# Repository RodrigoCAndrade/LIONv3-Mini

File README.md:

<div align="center">
  
</div>

<h1 align="center">LIONv3-Mini Module</h1>

<p align="center">

</p>

<br>

## Overview

The LIONv3-Mini is a miniaturized version of the [LIONv3-R](https://github.com/RodrigoCAndrade/LIONv3-Mini), without an onboard LoRa PCB antenna. Built around the ESP32-C6 with 16 MB of external flash, it offers local connectivity over Wi-Fi, Zigbee and Thread, plus LoRa and LR-FHSS for reliable Direct-to-Satellite (DtS) or terrestrial uplinks from remote sites at higher device densities than conventional LoRa. It is a scalable platform for telemetry, global asset tracking and remote sensing.

## Repository Organization

* `docs`: Systems engineering documentation, including schematics, datasheets, requirements (SRD), interface control (ICD) and diagrams.
* `hardware`: Native KiCad project and manufacturing files.
* `mechanics`: 3D models, technical drawings, and physical integration constraints.
* `software`: Embedded firmware and support testing scripts.

## Releases

<table>
  <thead>
    <tr>
      <th>Render</th>
      <th>Hardware Revision</th>
      <th>Status</th>
      <th>Latest Release</th>
      <th>Date</th>
      <th>Datasheet</th>
      <th>BOM</th>
      <th>Manufacturing Info</th>
    </tr>
  </thead>
  <tbody>
    <tr>
      <td></td>
      <td>LIONv3-Mini</td>
      <td>🚧 Development</td>
      <td><a href="#">-</a></td>
      <td>05-10-2026</td>
      <td><a href="#">PDF</a></td>
      <td><a href="hardware/Fabrication/BOM-LIONv3.csv">Available</a></td>
      <td><a href="hardware/Fabrication/GERBER-LIONv3.zip">Gerber</a></td>
    </tr>
  </tbody>
</table>

## Fabrication

This board is intended to be fabricated at [JLCPCB](https://jlcpcb.com/). The Gerber files, position files and BOM are available. For complete instructions, see the [Fabrication Guide](hardware/Fabrication/LIONv3-Mini%20Fabrication%20Guide.pdf). Please note that we do not guarantee the board will work, and any manufacturing issues are the user's responsibility. If you find an error or have suggestions for improvement, please do not hesitate to contribute.

## Contributing

We welcome contributions to this project! To ensure a smooth collaboration and maintain our engineering standards, please review our [Contribution Guidelines](CONTRIBUTING.md) before opening any issues, modifying the hardware design, or submitting pull requests.

## References

This board was developed from scratch, but draws on the earlier LIONv1 and LIONv2 designed by [Diego Anestor Coutinho](https://github.com/DIEGOVZK) and [Arielli Ajudarte](https://github.com/ari-aju). The v3 introduces several improvements:

- Dedicated low-power MCU on board
- LR-FHSS support and a more capable LoRa transceiver, covering both sub-GHz and S-band
- External flash for store-and-forward applications
- More compact form factor

## License

This project utilizes a dual-licensing approach to maximize flexibility and adoption:

* **Hardware:** The hardware designs and schematics are licensed under the permissive **[CERN-OHL-P-2.0](hardware/LICENSE)** open-hardware license. You are entirely free to use, modify, distribute, and commercialize the design without any copyleft obligations to share your derived works under the same terms.
* **Software:** All embedded firmware and utility scripts are licensed under the **[MIT License](software/LICENSE)**. You are free to use, modify, and distribute the code without restriction, provided the original copyright notice and permission notice are included.

## Acknowledgments

This work was carried out at the National Institute of Telecommunications (Inatel) with the support of three research laboratories. The EMBRAPII Inatel Competence Center for 5G and 6G Networks [(xGMobile)](https://inatel.br/xgmobile/) supported this project through its Talent Development Program (PFT xGMobile), alongside the Radio & Communication Laboratory [(RadioCom Lab)](https://inatel.br/radiocomlab/) and the Wireless and Artificial Intelligence Laboratory [(WAI Lab)](https://inatel.br/wailab/). Many thanks to the researchers and staff of all three laboratories for their help and for the infrastructure that made the LIONv3-Mini possible.

<p align="center">
  <sub>Built with ❤️ by <a href="https://rodrigoandrade.com">Rodrigo de Carvalho Andrade</a></sub>
</p>

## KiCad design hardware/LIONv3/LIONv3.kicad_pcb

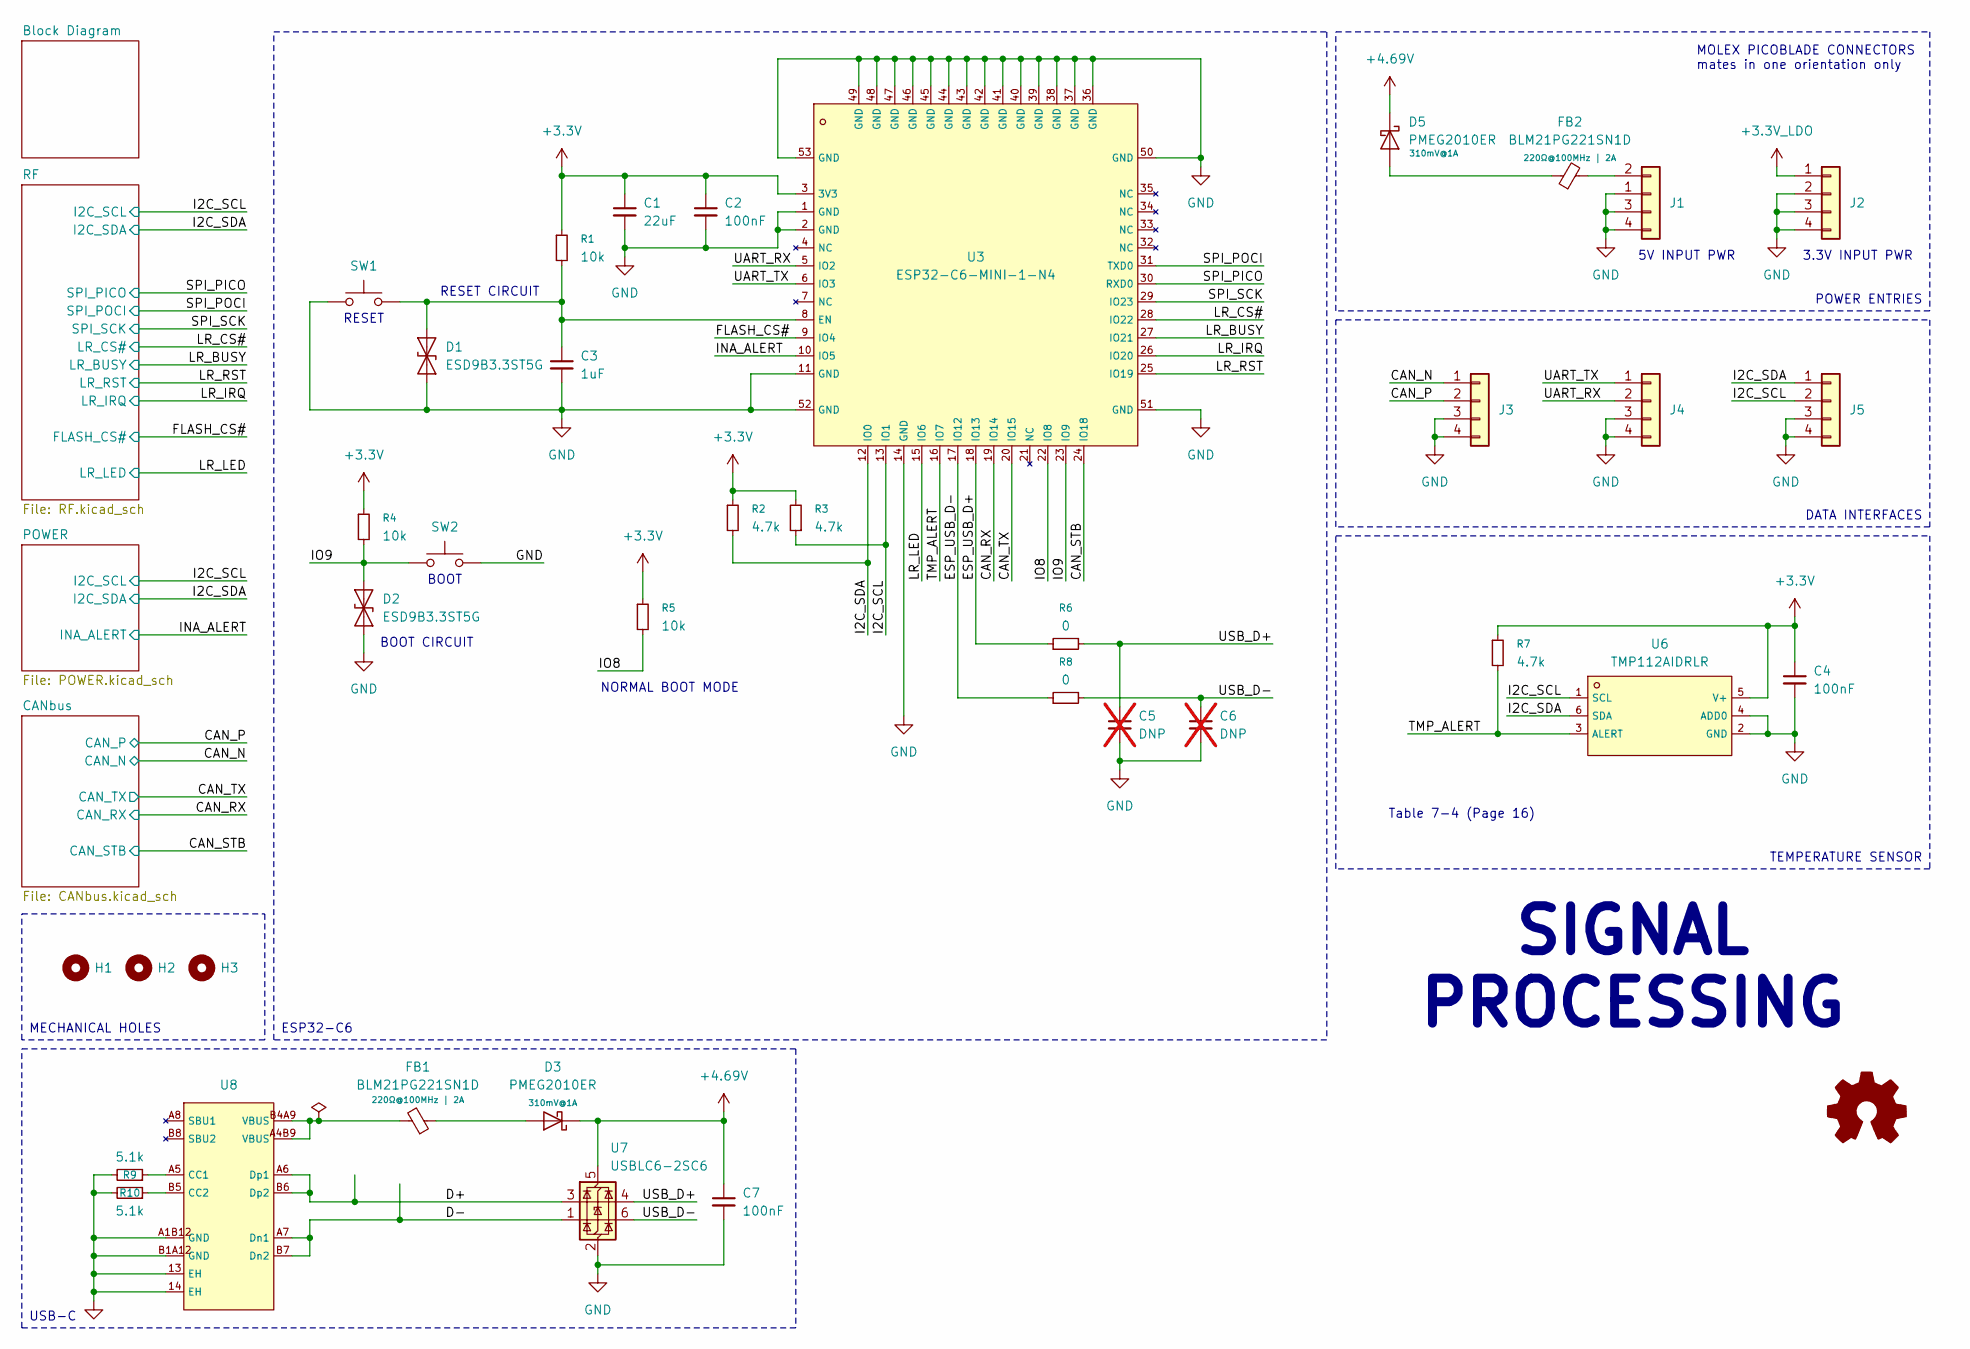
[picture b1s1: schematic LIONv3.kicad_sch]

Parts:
C1: 22uF; C_0805_2012Metric; LCSC C45783
C2, C4, C7: 100nF; C_0402_1005Metric; LCSC C307331
C3: 1uF; C_0603_1608Metric; LCSC C15849
C5, C6: DNP; C_0402_1005Metric; not fitted
D1, D2: ESD9B3.3ST5G; D_SOD-923; LCSC C96512
D3, D5: PMEG2010ER; Nexperia_CFP3_SOD-123W; Rating 310mV@1A; LCSC C82288
FB1, FB2: BLM21PG221SN1D; L_0805_2012Metric; Rating 220Ω@100MHz | 2A; LCSC C85840
H1, H2, H3: MountingHole_Pad; MountingHole_2.5mm
J1, J2, J3, J4, J5: 532610271; Molex_PicoBlade_53261-0271_1x02-1MP_P1.25mm_Horizontal; LCSC C177225
R1, R4, R5: 10k; R_0402_1005Metric; LCSC C25744
R2, R3, R7: 4.7k; R_0402_1005Metric; LCSC C25900
R6, R8: 0; R_0402_1005Metric; LCSC C17168
R9, R10: 5.1k; R_0402_1005Metric; LCSC C25905
S1: Logo_Open_Hardware_Small; OSHW-Logo2_14.6x12mm_SilkScreen
SW1, SW2: KEY-SMD_L3.9-W3.0-LS5.0; LCSC C5373431
U3: ESP32-C6-MINI-1-N4; ESP32-C6-MINI-1; LCSC C5736265
U6: TMP112AIDRLR; SOT-563_L1.6-W1.2-P0.50-LS1.6-BR; LCSC C28927
U7: USBLC6-2SC6; SOT-23-6; LCSC C7519
U8: TYPE-C_16PIN_2MD(073); USB-C-SMD_TYPE-C-16PIN-2MD-073; LCSC C2765186

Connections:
+3.3V: C1.1, C2.1, C4.1, R1.1, R2.1, R3.2, R4.1, R5.1, R7.1, U3.3 (3V3), U6.5 (V+); also elsewhere on the board
+3.3V_LDO: J2.1; also elsewhere on the board
+4.69V: C7.1, D3.1 (K), D5.1 (K), U7.5 (VBUS); also elsewhere on the board
/CAN_N: J3.1; also elsewhere on the board
/CAN_P: J3.2; also elsewhere on the board
/CAN_RX: U3.19 (IO14); also elsewhere on the board
/CAN_STB: U3.24 (IO18); also elsewhere on the board
/CAN_TX: U3.20 (IO15); also elsewhere on the board
/D+: U7.3 (I/O2), U8.A6 (Dp1), U8.B6 (Dp2)
/D-: U7.1 (I/O1), U8.A7 (Dn1), U8.B7 (Dn2)
/ESP_USB_D+: R6.1, U3.18 (IO13)
/ESP_USB_D-: R8.1, U3.17 (IO12)
/FLASH_CS#: U3.9 (IO4); also elsewhere on the board
/I2C_SCL: J5.2, R3.1, U3.13 (IO1), U6.1 (SCL); also elsewhere on the board
/I2C_SDA: J5.1, R2.2, U3.12 (IO0), U6.6 (SDA); also elsewhere on the board
/INA_ALERT: U3.10 (IO5); also elsewhere on the board
/IO8: R5.2, U3.22 (IO8)
/IO9: D2.2 (A2), R4.2, SW2.1, U3.23 (IO9)
/LR_BUSY: U3.27 (IO21); also elsewhere on the board
/LR_CS#: U3.28 (IO22); also elsewhere on the board
/LR_IRQ: U3.26 (IO20); also elsewhere on the board
/LR_LED: U3.15 (IO6); also elsewhere on the board
/LR_RST: U3.25 (IO19); also elsewhere on the board
/SPI_PICO: U3.30 (RXD0); also elsewhere on the board
/SPI_POCI: U3.31 (TXD0); also elsewhere on the board
/SPI_SCK: U3.29 (IO23); also elsewhere on the board
/TMP_ALERT: R7.2, U3.16 (IO7), U6.3 (ALERT)
/UART_RX: J4.2, U3.5 (IO2)
/UART_TX: J4.1, U3.6 (IO3)
/USB_D+: C5.1, R6.2, U7.4 (I/O2)
/USB_D-: C6.1, R8.2, U7.6 (I/O1)
GND: C1.2, C2.2, C3.2, C4.2, C5.2, C6.2, C7.2, D1.1 (A1), D2.1 (A1), J1.1, J1.3, J1.4, J2.2, J2.3, J2.4, J3.3, J3.4, J4.3, J4.4, J5.3, J5.4, R9.2, R10.2, SW1.1, SW2.2, U3.1 (GND), U3.2 (GND), U3.11 (GND), U3.14 (GND), U3.36 (GND), U3.37 (GND), U3.38 (GND), U3.39 (GND), U3.40 (GND), U3.41 (GND), U3.42 (GND), U3.43 (GND), U3.44 (GND), U3.45 (GND), U3.46 (GND), U3.47 (GND), U3.48 (GND), U3.49 (GND), U3.50 (GND), U3.51 (GND), U3.52 (GND), U3.53 (GND), U6.2 (GND), U6.4 (ADD0), U7.2 (GND), U8.13 (EH), U8.14 (EH), U8.A1B12 (GND), U8.B1A12 (GND); also elsewhere on the board
unnamed: C3.1, D1.2 (A2), R1.2, SW1.2, U3.8 (EN)
unnamed: D3.2 (A), FB1.1
unnamed: D5.2 (A), FB2.1
unnamed: FB1.2, U8.A4B9 (VBUS), U8.B4A9 (VBUS)
unnamed: FB2.2, J1.2
unnamed: R9.1, U8.A5 (CC1)
unnamed: R10.1, U8.B5 (CC2)

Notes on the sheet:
Table 7-4 (Page 16)
5V INPUT PWR
MOLEX PICOBLADE CONNECTORS mates in one orientation only
3.3V INPUT PWR
BOOT CIRCUIT
BOOT
SIGNAL PROCESSING
RESET CIRCUIT
NORMAL BOOT MODE
RESET
MECHANICAL HOLES
TEMPERATURE SENSOR
DATA INTERFACES
POWER ENTRIES
ESP32-C6
USB-C

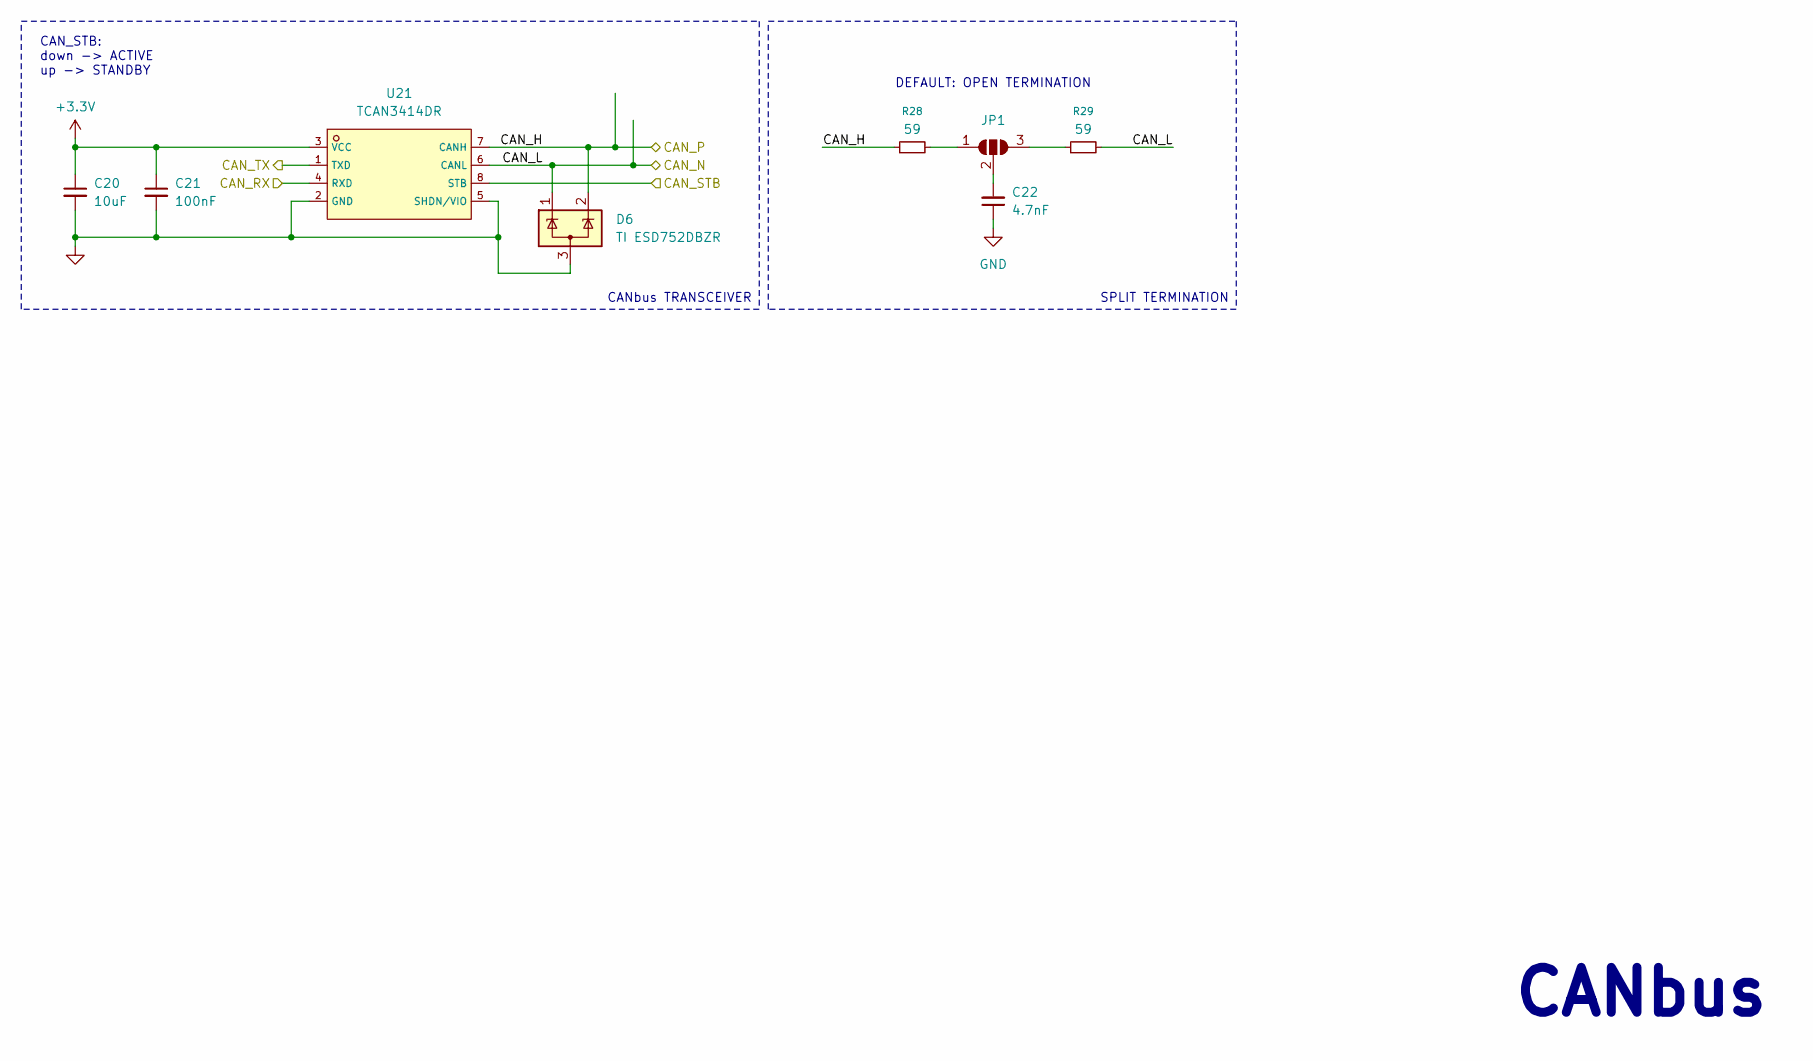
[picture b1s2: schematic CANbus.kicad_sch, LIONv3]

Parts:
C20: 10uF; C_0805_2012Metric; LCSC C440198
C21: 100nF; C_0402_1005Metric; LCSC C307331
C22: 4.7nF; C_0402_1005Metric; LCSC C1538
D6: TI ESD752DBZR; SOT-23-3; LCSC C20345397
JP1: SolderJumper_3_Open; SolderJumper-3_P2.0mm_Open_TrianglePad1.0x1.5mm
R28, R29: 59; R_0402_1005Metric; LCSC C227152
U21: TCAN3414DR; SOIC-8_L4.9-W3.9-P1.27-LS6.0-BL; LCSC C22396693

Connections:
+3.3V: C20.1, C21.1, U21.3 (VCC); also elsewhere on the board
/CAN_N: D6.1 (K), R29.2, U21.6 (CANL); also elsewhere on the board
/CAN_P: D6.2 (K), R28.1, U21.7 (CANH); also elsewhere on the board
/CAN_RX: U21.4 (RXD); also elsewhere on the board
/CAN_STB: U21.8 (STB); also elsewhere on the board
/CAN_TX: U21.1 (TXD); also elsewhere on the board
GND: C20.2, C21.2, C22.1, D6.3 (A), U21.2 (GND), U21.5 (SHDN/VIO); also elsewhere on the board
unnamed: JP1.1 (A), R28.2
unnamed: JP1.3 (B), R29.1
unnamed: C22.2, JP1.2 (C)

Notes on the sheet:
CAN_STB: down -> ACTIVE up -> STANDBY
CANbus
DEFAULT: OPEN TERMINATION
CANbus TRANSCEIVER
SPLIT TERMINATION

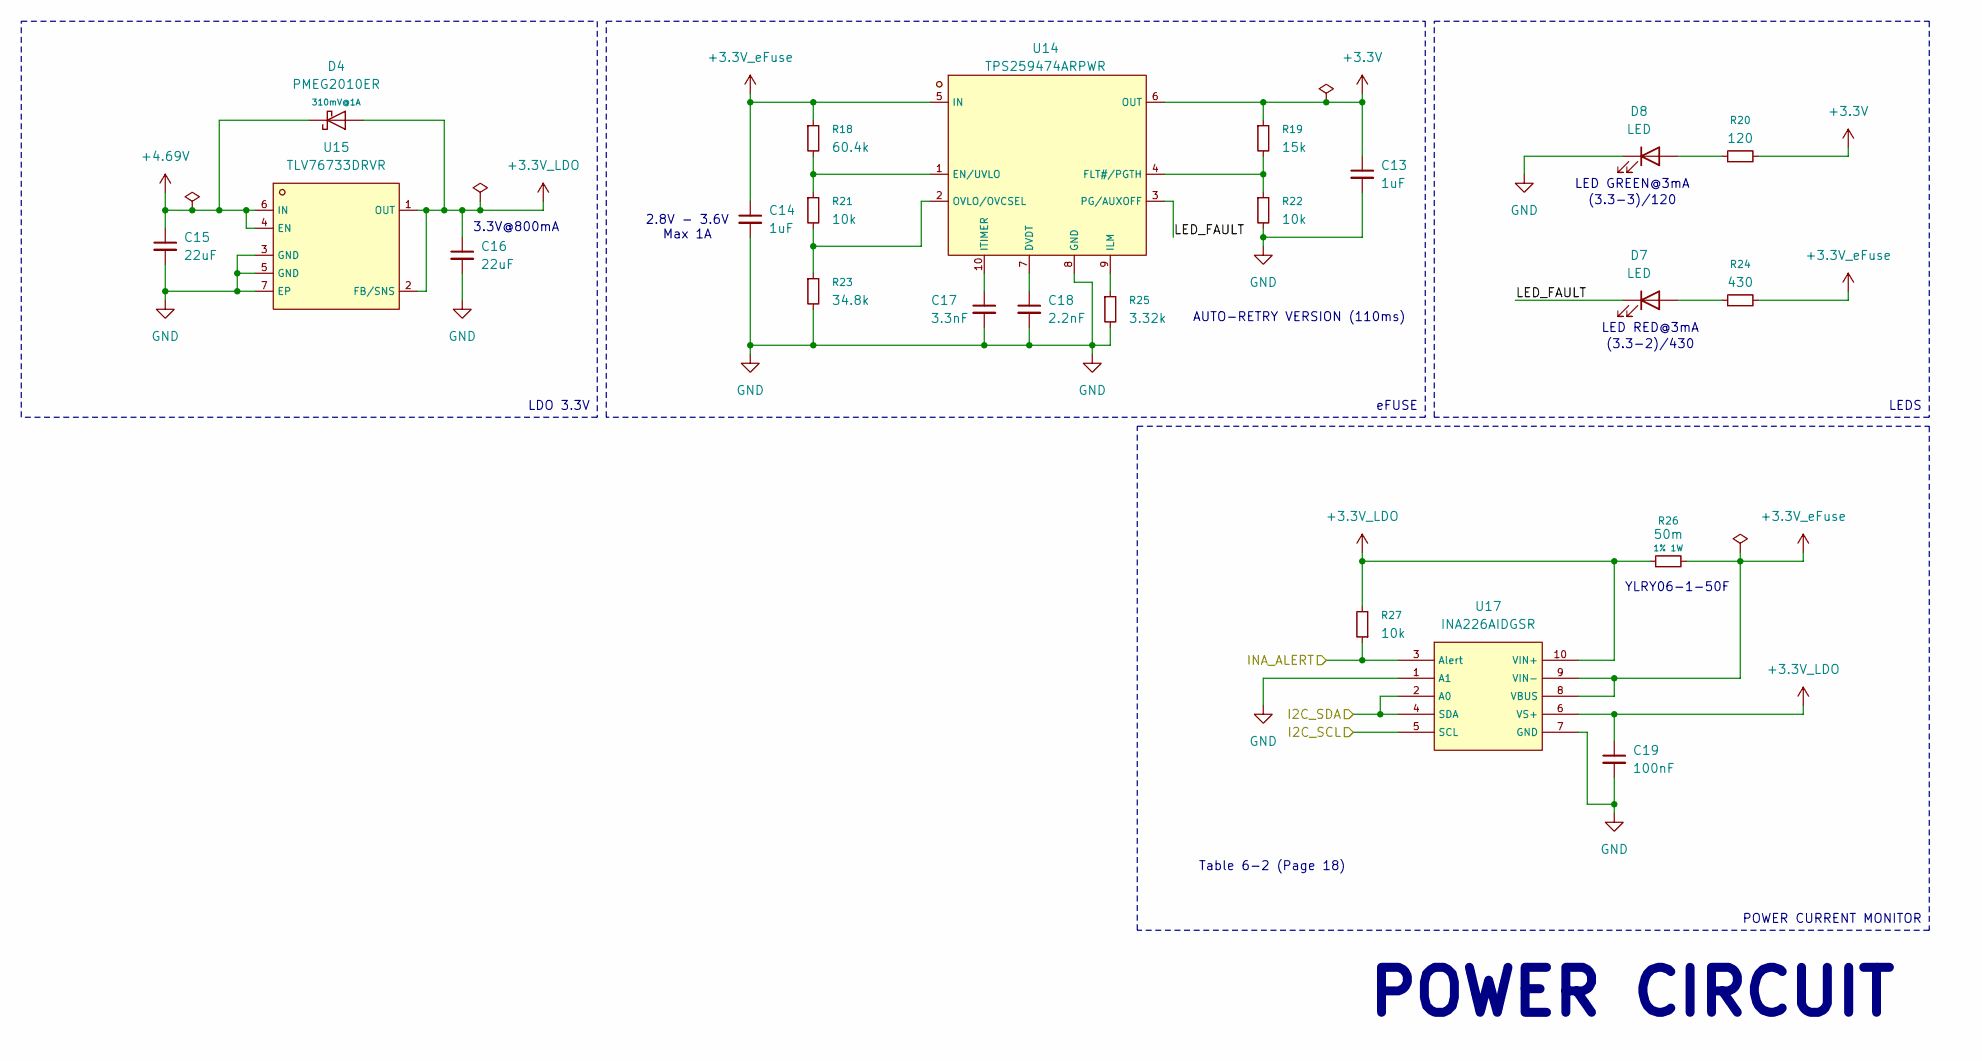
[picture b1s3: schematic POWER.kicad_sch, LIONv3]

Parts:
C13, C14: 1uF; C_0603_1608Metric; LCSC C15849
C15, C16: 22uF; C_0805_2012Metric; LCSC C45783
C17: 3.3nF; C_0402_1005Metric; LCSC C3881585
C18: 2.2nF; C_0402_1005Metric; LCSC C2987940
C19: 100nF; C_0402_1005Metric; LCSC C307331
D4: PMEG2010ER; Nexperia_CFP3_SOD-123W; Rating 310mV@1A; LCSC C82288
D7: LED; LED_0603_1608Metric; LCSC C965799
D8: LED; LED_0603_1608Metric; LCSC C965804
R18: 60.4k; R_0402_1005Metric; LCSC C2998058
R19: 15k; R_0402_1005Metric; LCSC C25756
R20: 120; R_0402_1005Metric; LCSC C2909389
R21, R22, R27: 10k; R_0402_1005Metric; LCSC C25744
R23: 34.8k; R_0402_1005Metric; LCSC C2076772
R24: 430; R_0402_1005Metric; LCSC C2909321
R25: 3.32k; R_0402_1005Metric; LCSC C2998161
R26: 50m; R1206; Tolerance 1%; Rating ${Tolerance} ${Rated_Power}; LCSC C20608719
U14: TPS259474ARPWR; VQFN-10_L2.0-W2.0-P0.45-TL; LCSC C3662807
U15: TLV76733DRVR; WSON-6_L2.0-W2.0-P0.65-TL-EP; LCSC C2848334
U17: INA226AIDGSR; MSOP-10_L3.0-W3.0-P0.50-LS5.0-BL; LCSC C49851

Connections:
+3.3V: C13.1, R19.1, R20.2, U14.6 (OUT); also elsewhere on the board
+3.3V_LDO: C16.1, C19.1, D4.2 (A), R26.1, R27.2, U15.1 (OUT), U15.2 (FB/SNS), U17.6 (VS+), U17.10 (VIN+); also elsewhere on the board
+3.3V_eFuse: C14.1, R18.1, R24.2, R26.2, U14.5 (IN), U17.8 (VBUS), U17.9 (VIN-)
+4.69V: C15.1, D4.1 (K), U15.4 (EN), U15.6 (IN); also elsewhere on the board
/I2C_SCL: U17.5 (SCL); also elsewhere on the board
/I2C_SDA: U17.2 (A0), U17.4 (SDA); also elsewhere on the board
/INA_ALERT: R27.1, U17.3 (Alert); also elsewhere on the board
/POWER/LED_FAULT: D7.1 (K), U14.3 (PG/AUXOFF)
GND: C13.2, C14.2, C15.2, C16.2, C17.2, C18.2, C19.2, D8.1 (K), R22.2, R23.2, R25.2, U14.8 (GND), U15.3 (GND), U15.5 (GND), U15.7 (EP), U17.1 (A1), U17.7 (GND); also elsewhere on the board
unnamed: D7.2 (A), R24.1
unnamed: D8.2 (A), R20.1
unnamed: C18.1, U14.7 (DVDT)
unnamed: R18.2, R21.1, U14.1 (EN/UVLO)
unnamed: R19.2, R22.1, U14.4 (FLT#/PGTH)
unnamed: R25.1, U14.9 (ILM)
unnamed: C17.1, U14.10 (ITIMER)
unnamed: R21.2, R23.1, U14.2 (OVLO/OVCSEL)

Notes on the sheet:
POWER CIRCUIT
3.3V@800mA
2.8V - 3.6V Max 1A
(3.3-3)/120
AUTO-RETRY VERSION (110ms)
LED GREEN@3mA
LED RED@3mA
YLRY06-1-50F
(3.3-2)/430
Table 6-2 (Page 18)
POWER CURRENT MONITOR
LEDS
LDO 3.3V
eFUSE

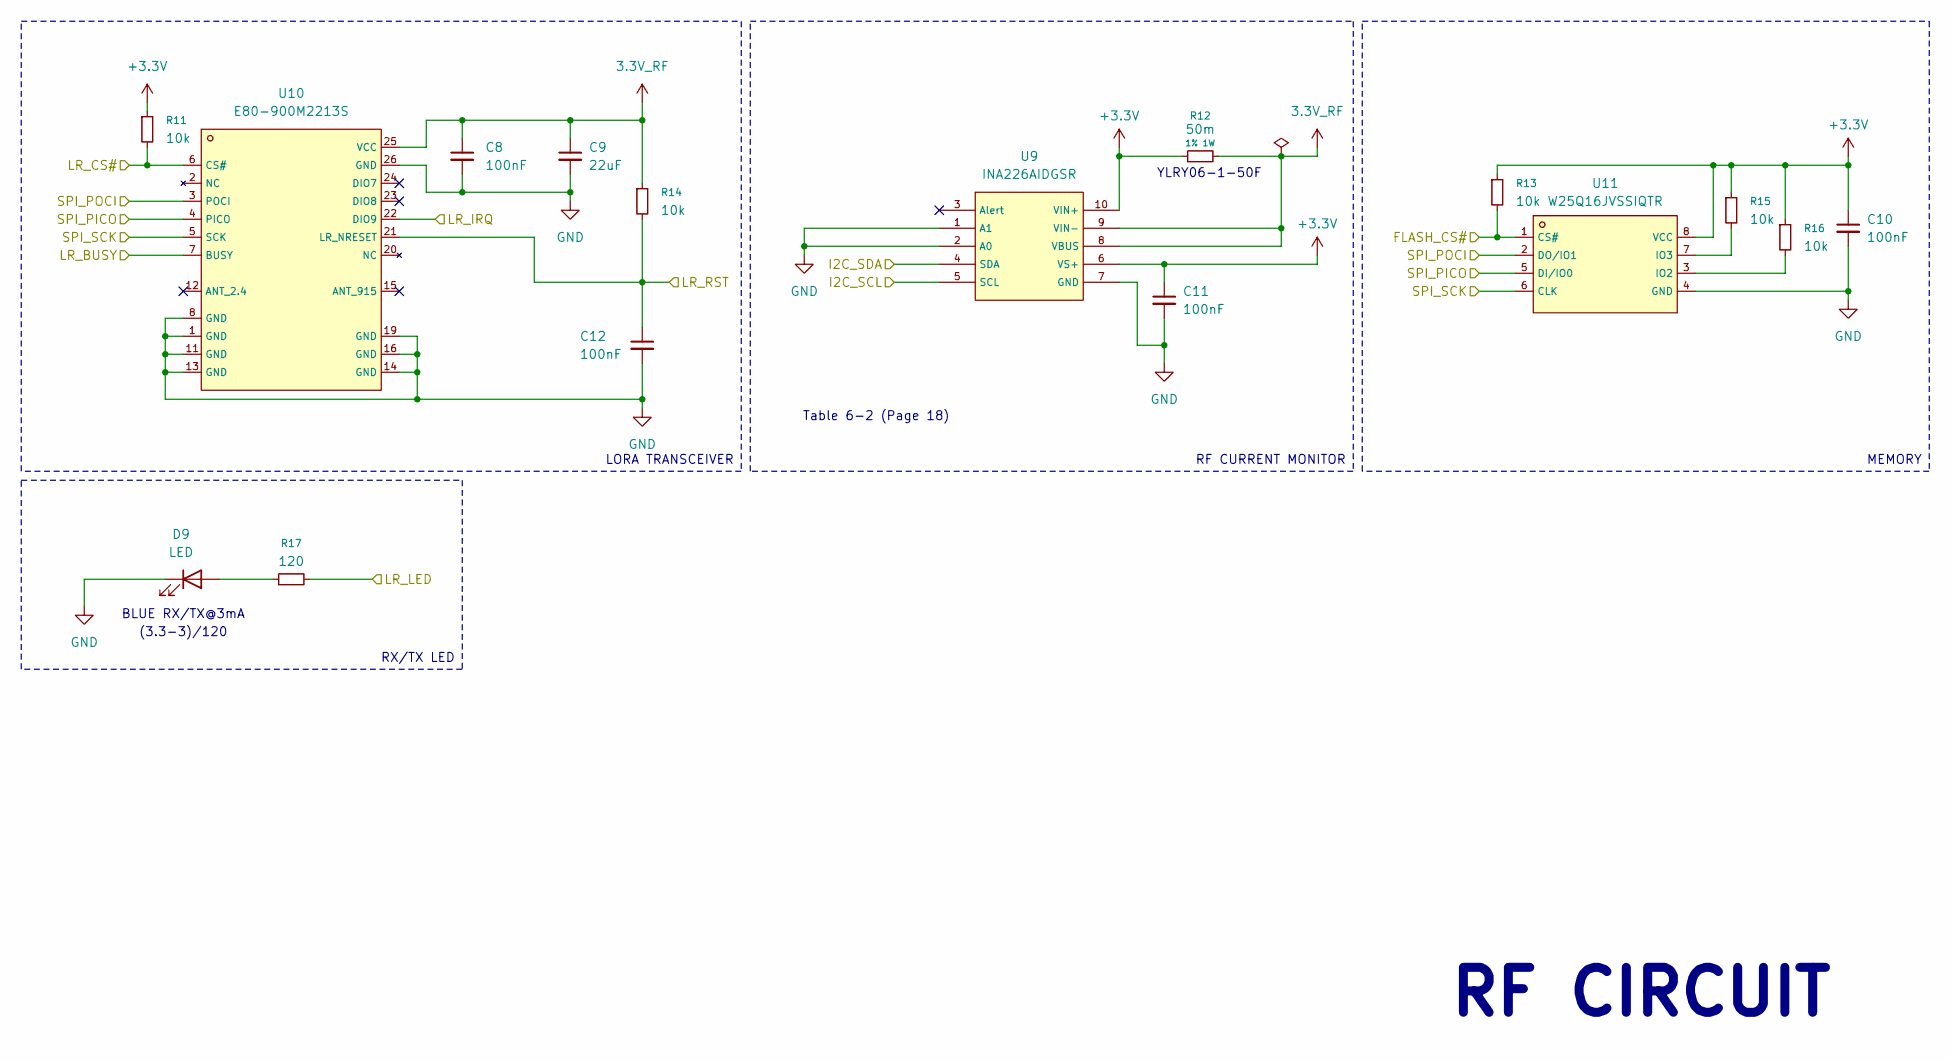
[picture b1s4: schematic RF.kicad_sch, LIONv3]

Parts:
C8, C10, C11, C12: 100nF; C_0402_1005Metric; LCSC C307331
C9: 22uF; C_0805_2012Metric; LCSC C45783
D9: LED; LED_0603_1608Metric; LCSC C965807
R11, R13, R14, R15, R16: 10k; R_0402_1005Metric; LCSC C25744
R12: 50m; R1206; Tolerance 1%; Rating ${Tolerance} ${Rated_Power}; LCSC C20608719
R17: 120; R_0402_1005Metric; LCSC C2909380
U9: INA226AIDGSR; MSOP-10_L3.0-W3.0-P0.50-LS5.0-BL; LCSC C49851
U10: E80-900M2213S; WIFIM-SMD_22P-L26.0-W16.0-P1.27-TL; LCSC C42464134
U11: W25Q16JVSSIQTR; SOIC-8_L5.3-W5.3-P1.27-LS8.0-BL; LCSC C131025

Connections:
3.3V_RF: C8.1, C9.1, R12.2, R14.1, U9.8 (VBUS), U9.9 (VIN-), U10.25 (VCC)
+3.3V: C10.1, C11.1, R11.1, R12.1, R13.1, R15.1, R16.1, U9.6 (VS+), U9.10 (VIN+), U11.8 (VCC); also elsewhere on the board
/FLASH_CS#: R13.2, U11.1 (CS#); also elsewhere on the board
/I2C_SCL: U9.5 (SCL); also elsewhere on the board
/I2C_SDA: U9.4 (SDA); also elsewhere on the board
/LR_BUSY: U10.7 (BUSY); also elsewhere on the board
/LR_CS#: R11.2, U10.6 (CS#); also elsewhere on the board
/LR_IRQ: U10.22 (DIO9); also elsewhere on the board
/LR_LED: R17.2; also elsewhere on the board
/LR_RST: C12.1, R14.2, U10.21 (LR_NRESET); also elsewhere on the board
/SPI_PICO: U10.4 (PICO), U11.5 (DI/IO0); also elsewhere on the board
/SPI_POCI: U10.3 (POCI), U11.2 (DO/IO1); also elsewhere on the board
/SPI_SCK: U10.5 (SCK), U11.6 (CLK); also elsewhere on the board
GND: C8.2, C9.2, C10.2, C11.2, C12.2, D9.1 (K), U9.1 (A1), U9.2 (A0), U9.7 (GND), U10.1 (GND), U10.8 (GND), U10.11 (GND), U10.13 (GND), U10.14 (GND), U10.16 (GND), U10.19 (GND), U10.26 (GND), U11.4 (GND); also elsewhere on the board
unnamed: D9.2 (A), R17.1
unnamed: R16.2, U11.3 (IO2)
unnamed: R15.2, U11.7 (IO3)

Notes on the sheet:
BLUE RX/TX@3mA
RF CIRCUIT
Table 6-2 (Page 18)
(3.3-3)/120
YLRY06-1-50F
MEMORY
RX/TX LED
RF CURRENT MONITOR
LORA TRANSCEIVER

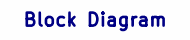
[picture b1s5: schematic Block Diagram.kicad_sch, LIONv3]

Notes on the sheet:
Block Diagram

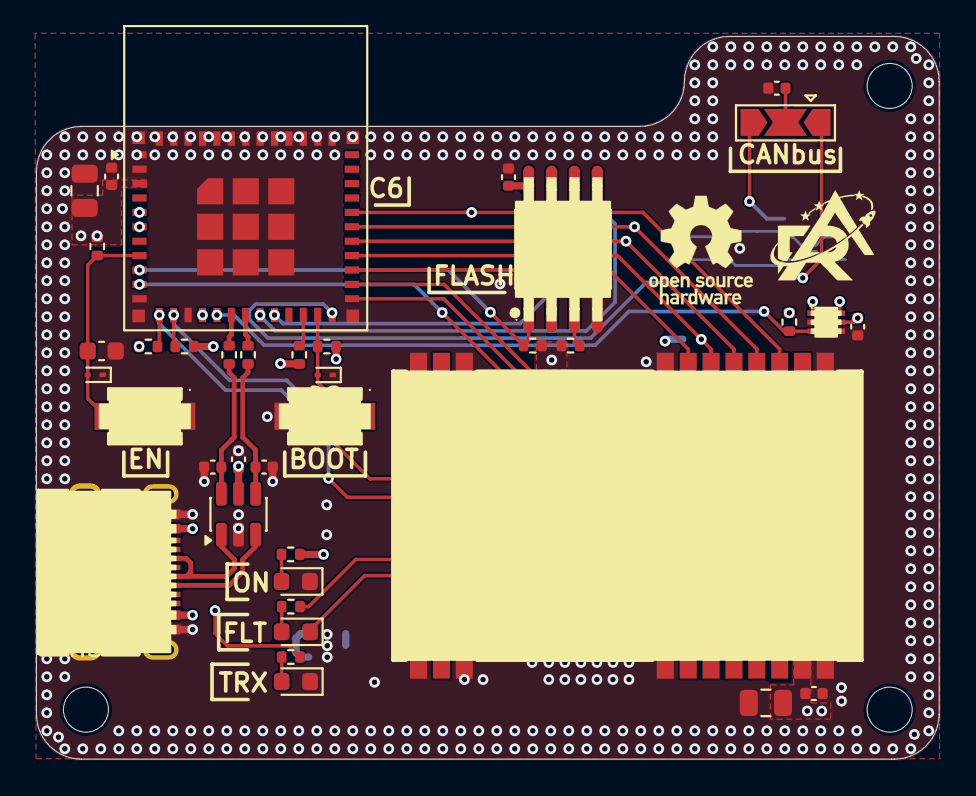
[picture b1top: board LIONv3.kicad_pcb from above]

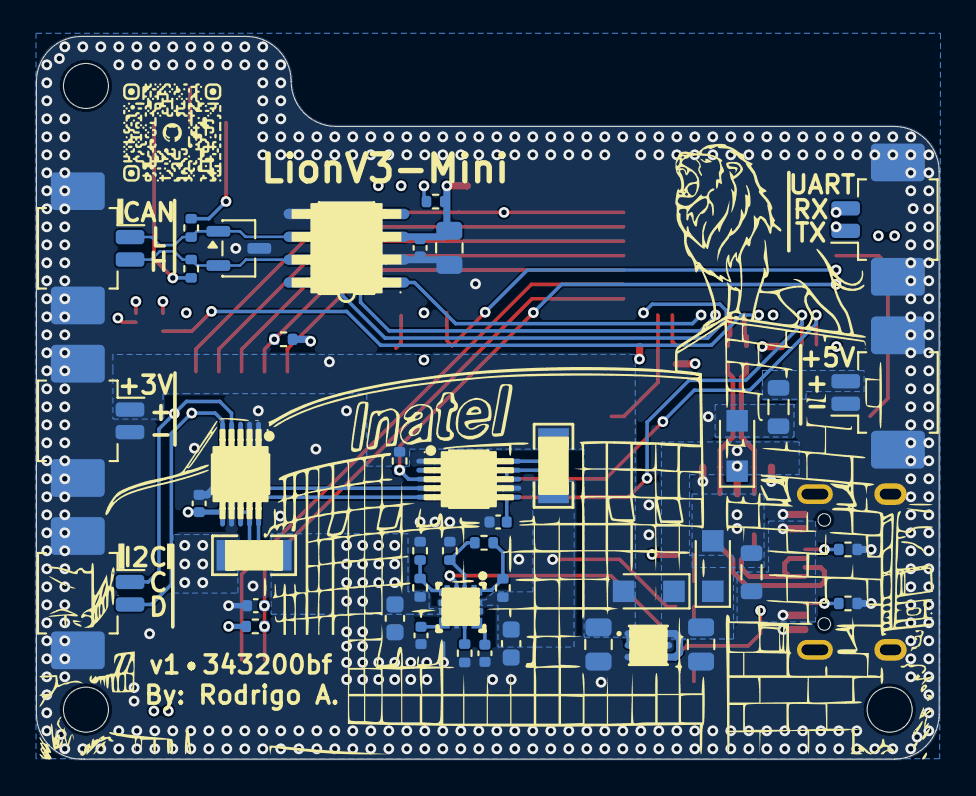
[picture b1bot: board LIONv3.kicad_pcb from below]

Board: 4 copper layers, 50.2 x 40.2 mm, 84 parts (43 on the bottom side), 56 nets.
